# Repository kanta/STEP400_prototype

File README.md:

## STEP400_prototype

This repository has been retained for data storage, but is no longer being updated.

Please visit https://github.com/ponoor/STEP400.

---

STEP400 is a 4-axis stepper motor driver designed for art or design projects. STEP400 combines the following elements into one single board:

- [Arduino Zero](https://www.arduino.cc/en/Guide/ArduinoZero)
- Ethernet shield
- Four stepper motor drivers
- Sensor inputs for homing and limiting

The current firmware is focused on working with [Open Sound Control](http://opensoundcontrol.org/) (OSC) via Ethernet, which is a common protocol for creative coding environments, like openFrameworks, Processing, Max, Unity, or Touch Designer.

Stepper driver chips are STMicroelectronics's [powerSTEP01](https://www.st.com/en/motor-drivers/powerstep01.html) which provide most of functionalities as a stepper driver.

## Repository Contents

This repo is temporal place for working. All information will be moved to a new repo when the clean up is done.

### Firmware
[/rev4/STEP400_proto_r4_firmware/STEP400_proto_r4_firmware/](https://github.com/kanta/STEP400_prototype/tree/master/rev4/STEP400_proto_r4_firmware/STEP400_proto_r4_firmware)

Source files for the firmware. Some Visual Studio files are included but you can open .ino file with Arduino IDE.

### Hardware
[/rev4/hardware/](https://github.com/kanta/STEP400_prototype/tree/master/rev4/hardware)

PCB design files for Eagle.

## Firmware dependency
- **[OSC Library](https://github.com/CNMAT/OSC)** from CNMAT
- **[Ponoor PowerSTEP01 Library](https://github.com/ponoor/Ponoor_PowerSTEP01_Library)**
- **[ArduinoJSON Library](https://arduinojson.org/)**
- **[Adafruit SleepyDog Arduino Library](https://github.com/adafruit/Adafruit_SleepyDog)**

## Examples
### Max
https://github.com/kanta/STEP400_prototype/blob/master/rev4/STEP400_proto_r4.maxpat

### openFrameworks
https://github.com/ponoor/step-series-example-openFrameworks

### Unity
https://github.com/ponoor/step-series-example-Unity

### Touch Designer
https://github.com/ponoor/step-series-example-TouchDesigner

## Documentation
Now working on [Wiki](https://github.com/kanta/STEP400_prototype/wiki).

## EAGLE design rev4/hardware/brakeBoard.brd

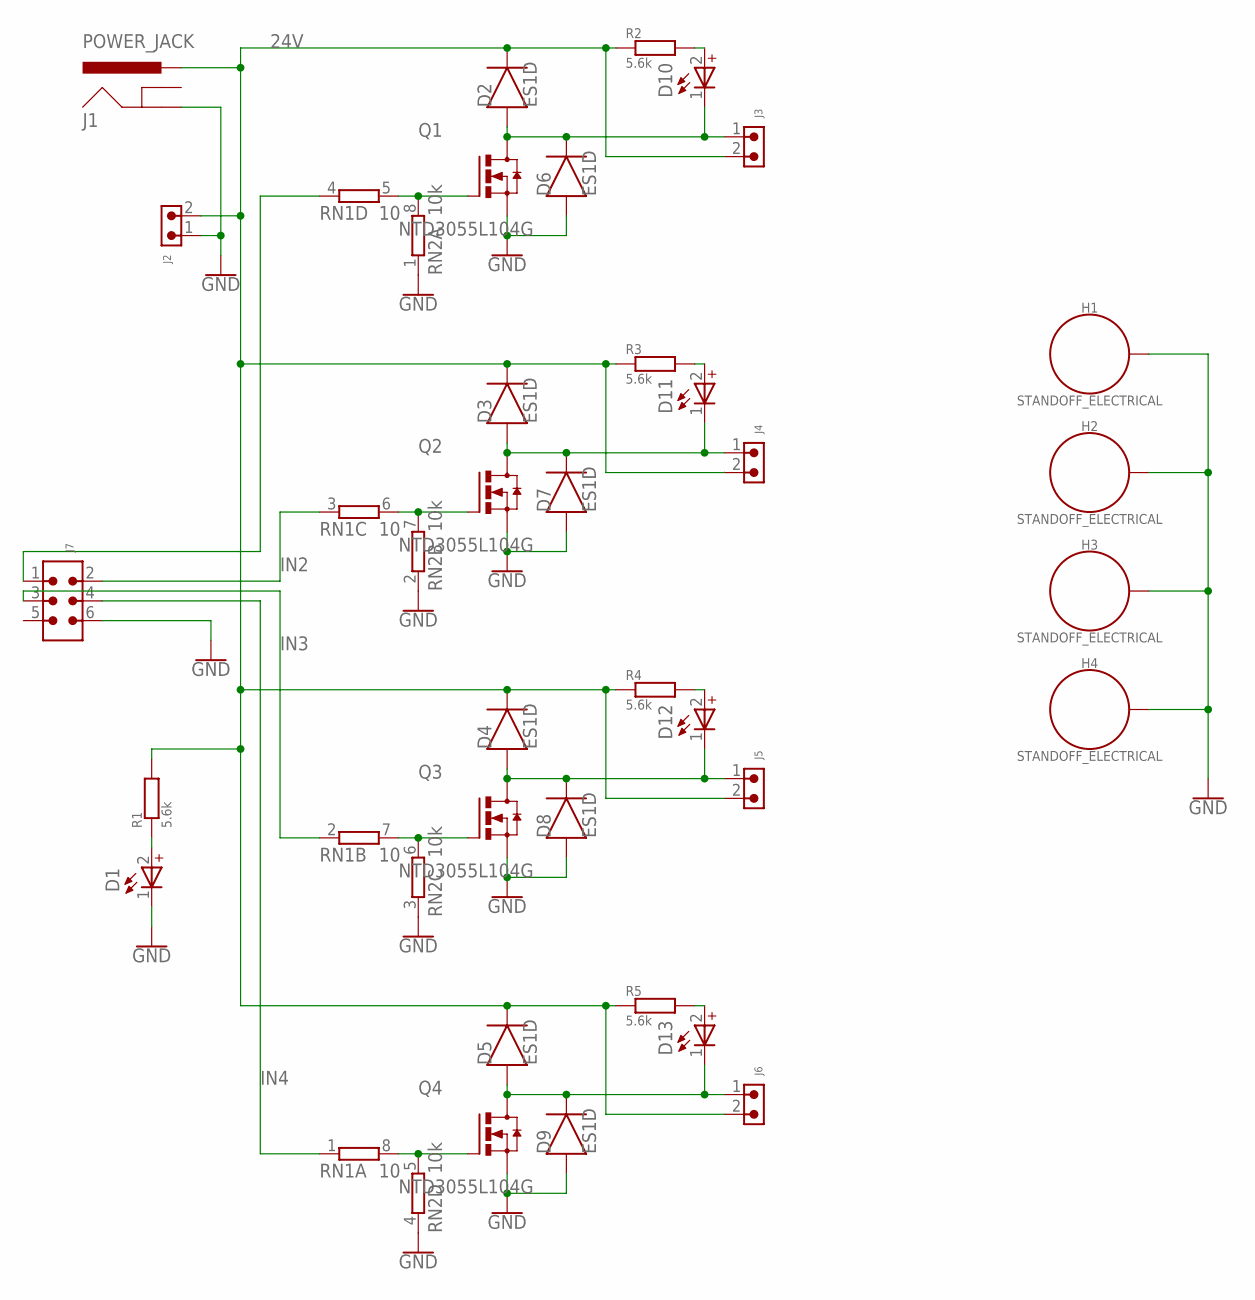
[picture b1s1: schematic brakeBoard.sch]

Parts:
D1, D10, D11, D12, D13: WL-SMCD_0603_150060GS55040; WL-SMCD_0603
D2, D3, D4, D5, D6, D7, D8, D9: ES1D; DIOM5226X290N
H1, H2, H3, H4: STANDOFF_ELECTRICAL; STANDOFF-ELECTRICAL
J1: POWER_JACK; POWER_JACK_PTH
J2: 691322310002
J3, J4, J5, J6: 691321300002
J7: 6120XX21621_61200621621; 61200621621
Q1, Q2, Q3, Q4: NTD3055L104G; DPAK3
R1, R2, R3, R4, R5: 5.6k; RESC2012X65
RN1: 10; CAY16_LONG_W
RN2: 10k; CAY16_LONG_W

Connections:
24V: D2.1 (C), D3.1 (C), D4.1 (C), D5.1 (C), J1.PWR, J2.2, J3.2, J4.2, J5.2, J6.2, R1.2, R2.1, R3.1, R4.1, R5.1
GND: D1.1 (_), D6.2 (A), D7.2 (A), D8.2 (A), D9.2 (A), H1.P1, H2.P1, H3.P1, H4.P1, J1.GND, J2.1, J7.6, Q1.2 (S), Q2.2 (S), Q3.2 (S), Q4.2 (S), RN2.1, RN2.2 (1), RN2.3 (1), RN2.4 (1)
IN1: J7.1, RN1.4 (1)
IN2: J7.2, RN1.3 (1)
IN3: J7.3, RN1.2 (1)
IN4: J7.4, RN1.1
unnamed: D2.2 (A), D6.1 (C), D10.1 (_), J3.1, Q1.3 (D)
unnamed: D10.2 (+), R2.2
unnamed: Q1.1 (G), RN1.5 (2), RN2.8 (2)
unnamed: D3.2 (A), D7.1 (C), D11.1 (_), J4.1, Q2.3 (D)
unnamed: D11.2 (+), R3.2
unnamed: D4.2 (A), D8.1 (C), D12.1 (_), J5.1, Q3.3 (D)
unnamed: D12.2 (+), R4.2
unnamed: D5.2 (A), D9.1 (C), D13.1 (_), J6.1, Q4.3 (D)
unnamed: D13.2 (+), R5.2
unnamed: Q4.1 (G), RN1.8 (2), RN2.5 (2)
unnamed: Q3.1 (G), RN1.7 (2), RN2.6 (2)
unnamed: Q2.1 (G), RN1.6 (2), RN2.7 (2)
unnamed: D1.2 (+), R1.1

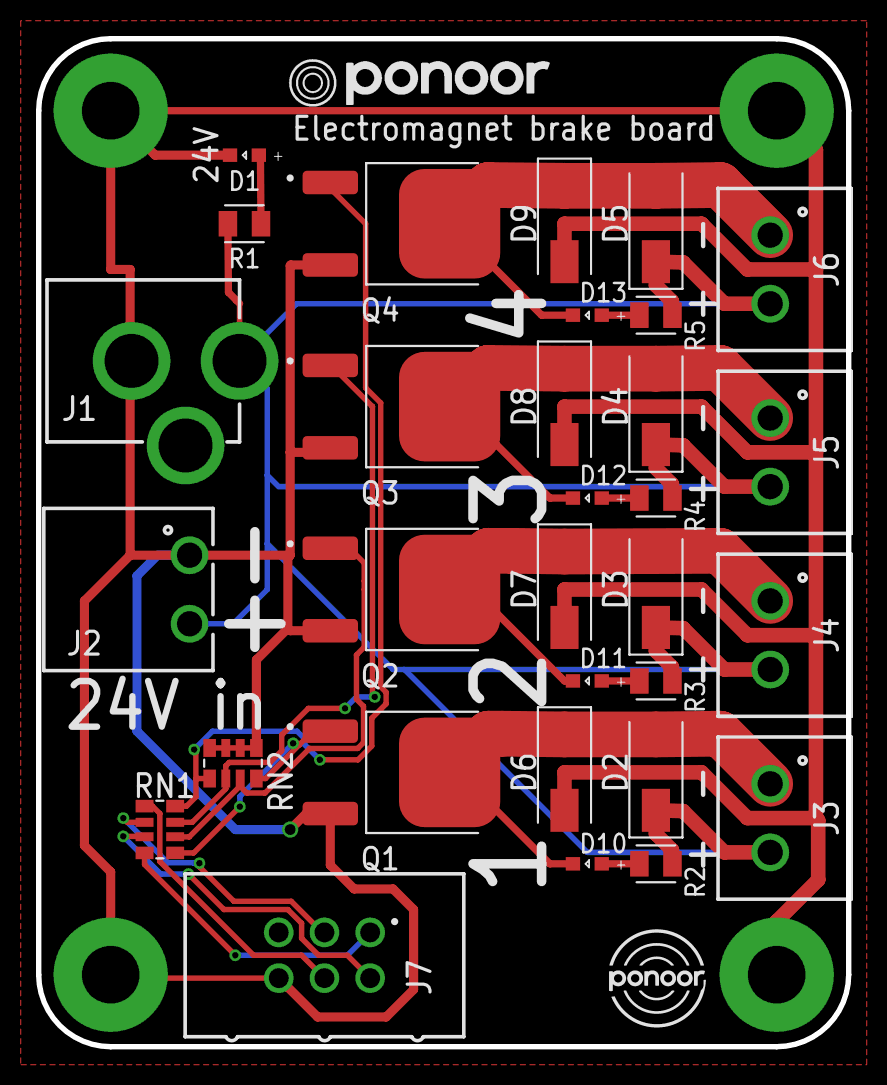
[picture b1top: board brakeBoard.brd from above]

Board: 2 copper layers, 45.0 x 56.0 mm, 38 parts (1 on the bottom side), 19 nets.

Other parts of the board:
U$1: PONOOR_LOGO_6MM
U$2, U$3: PONOOR_TEXT_15MM

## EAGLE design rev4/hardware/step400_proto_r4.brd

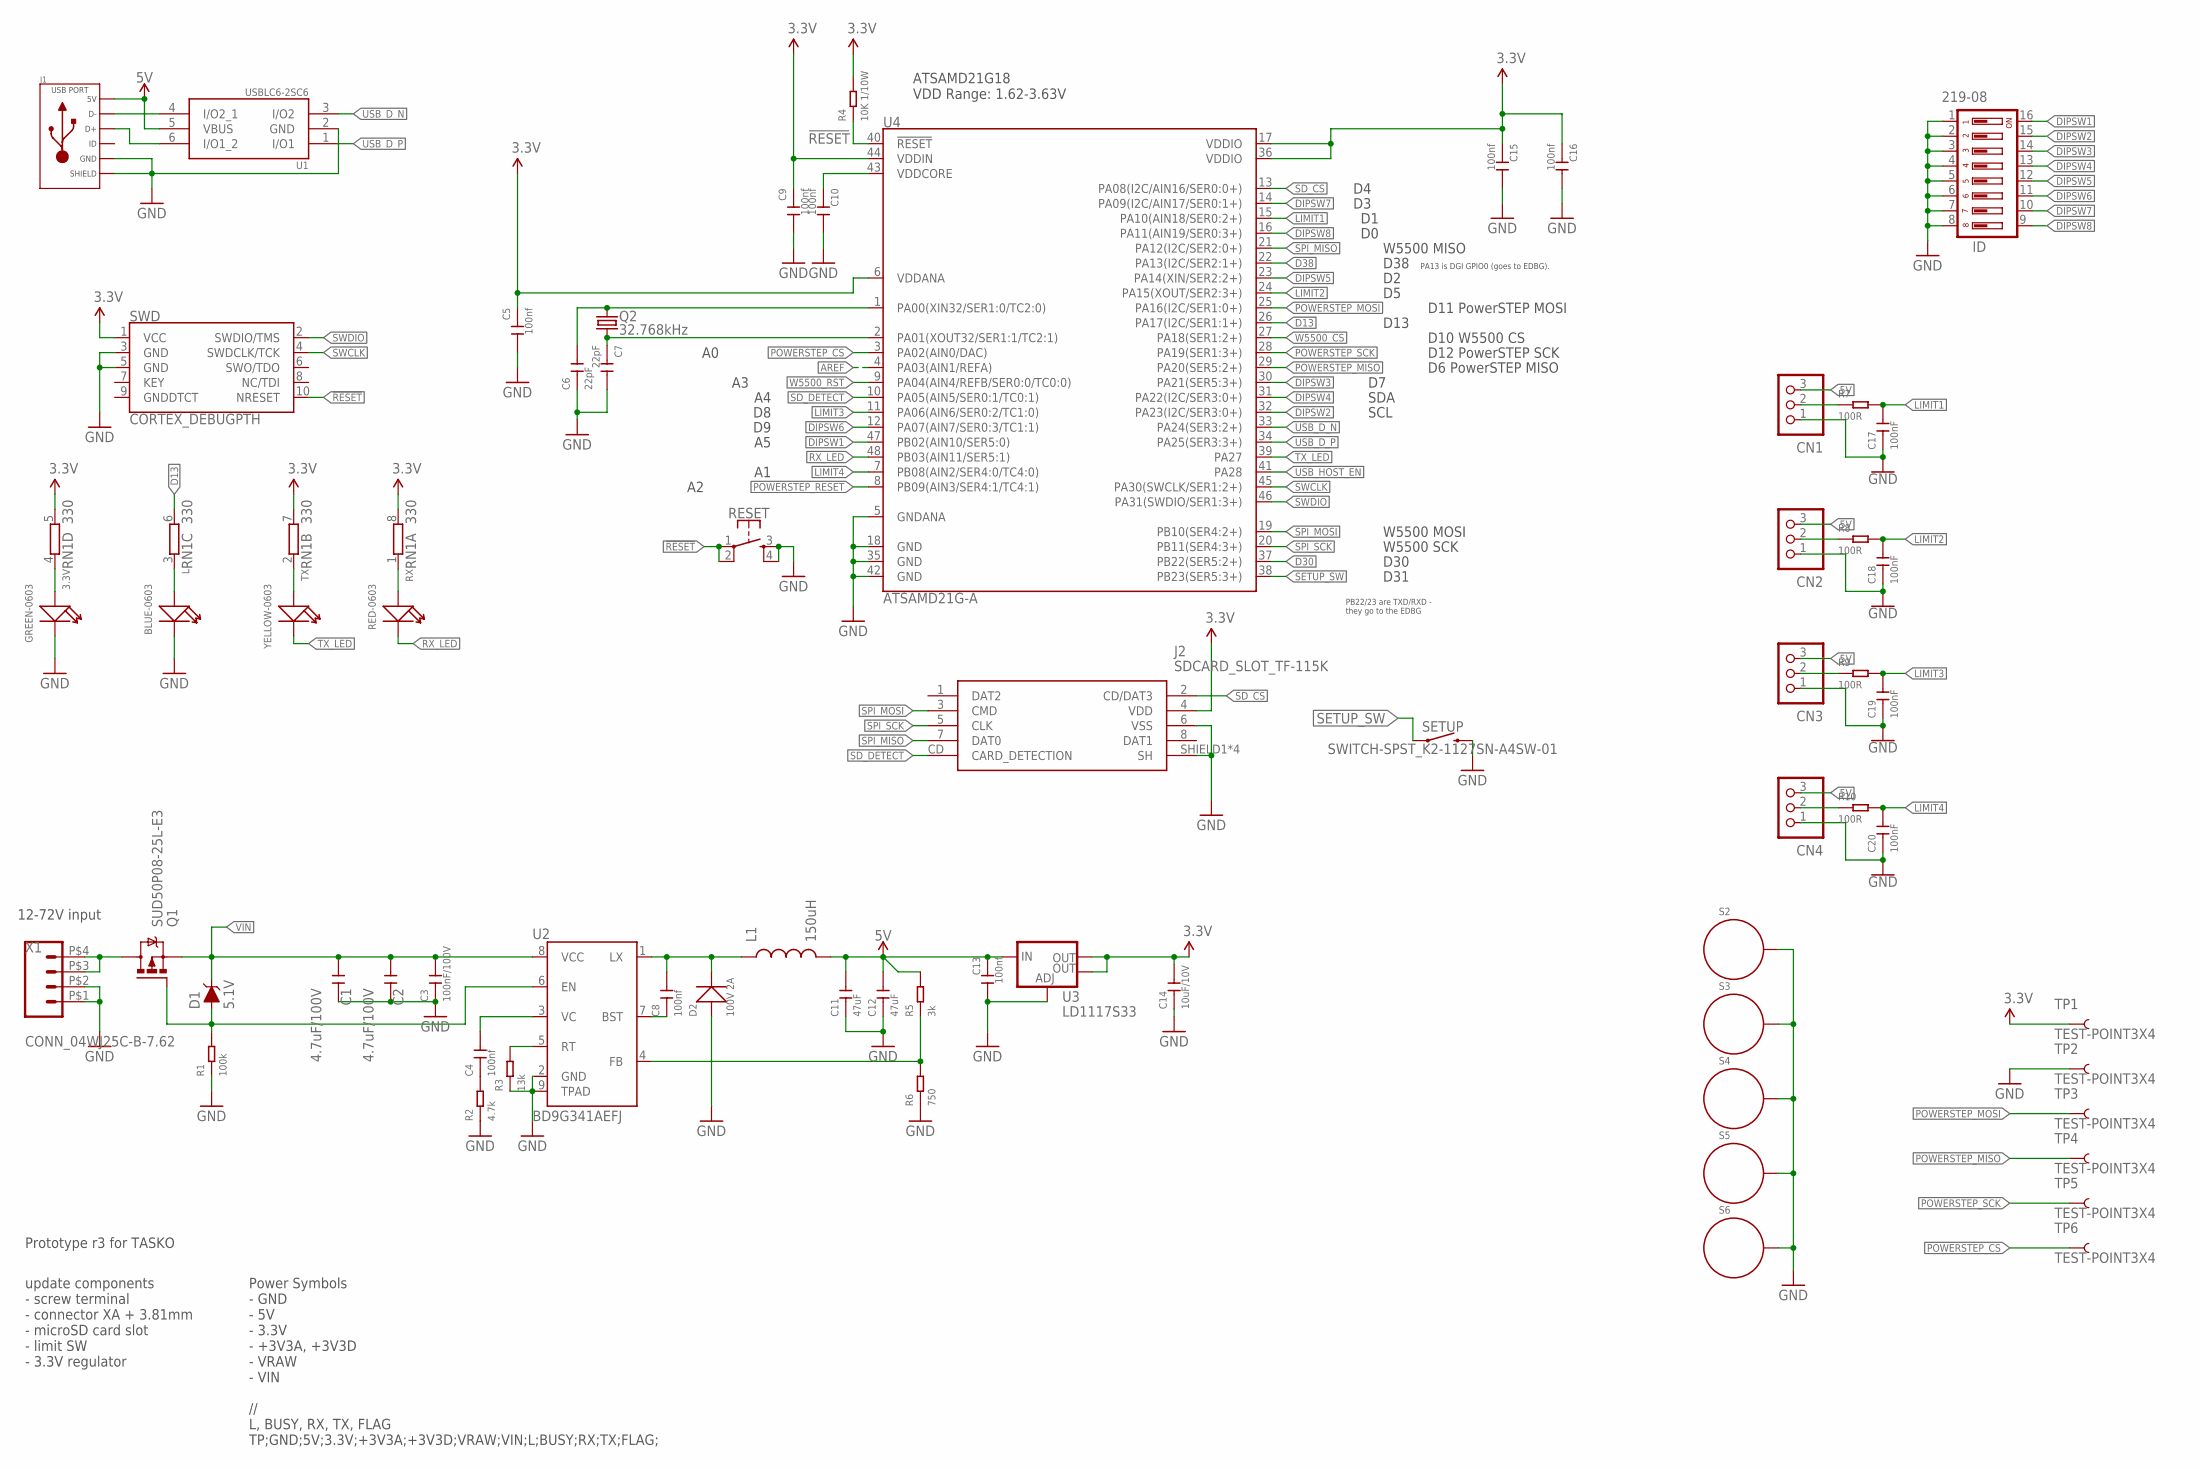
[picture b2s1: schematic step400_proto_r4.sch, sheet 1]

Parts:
3.3V: GREEN-0603; LED-0603
C1, C2: 4.7uF/100V; C1210
C3: 100nF/100V; C0805
C4, C8: 100nf; C0603
C5, C9, C10, C13, C15, C16: 100nf; C0402
C6, C7: 22pF; C0402
C11, C12: 47uF; C1206
C14: 10uF/10V; C0805
C17, C18, C19, C20: 100nF; C0402
CN1, CN2, CN3, CN4: B3B-XASK-1
D1: 5.1V; SOD-323
D2: 100V 2A; DO-214AC
ID: 219-08; CTS-219-08
J1: USB_MICRO_10118193-0001LF; MICROUSB-FCI-PBAN
J2: SDCARD_SLOT_TF-115K; TF-115K
L: BLUE-0603; LED-0603
L1: 150uH; L5045_L
Q1: SUD50P08-25L-E3; D-PAK_TO252AA
Q2: 32.768kHz; FC-135
R1: 100k; R0603
R2: 4.7k; R0603
R3: 13k; R0603
R4: 10K 1/10W; R0603
R5: 3k; R0603
R6: 750; R0603
R7, R8, R9, R10: 100R; R0603
RESET: MOMENTARY-SWITCH-SPST-2-SMD-5.2MM; TACTILE_SWITCH_SMD_5.2MM
RN1: 330; CAY16_LONG_W
RX: RED-0603; LED-0603
S2, S3, S4, S5, S6: STANDOFF_ELECTRICAL; STANDOFF-ELECTRICAL
SETUP: SWITCH-SPST_K2-1127SN-A4SW-01; K2-1127SN-A4SW-01
SWD: CORTEX_DEBUGPTH; 2X5-PTH-1.27MM
TP1, TP2, TP3, TP4, TP5, TP6: TEST-POINT3X4; PAD.03X.04
TX: YELLOW-0603; LED-0603
U1: USBLC6-2SC6; SOT23-6L
U2: BD9G341AEFJ; SOIC127P600X100-9N
U3: LD1117S33; SOT223
U4: ATSAMD21G-A; TQFP-48
X1: CONN_04WJ25C-B-7.62; WJ25C-B-7.62-4P

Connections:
3.3V: C5.1, C9.1, C14.2, C15.1, C16.1, J2.4 (VDD), R4.2, RN1.5 (2), RN1.7 (2), RN1.8 (2), SWD.1 (VCC), TP1.P$1, U3.2 (OUT), U3.4 (OUT), U4.6 (VDDANA), U4.17 (VDDIO), U4.36 (VDDIO), U4.44 (VDDIN); also elsewhere on the board
5V: C11.2, C12.2, C13.1, CN1.3, CN2.3, CN3.3, CN4.3, J1.1 (5V), L1.P$2 (2), R5.2, U1.5 (VBUS), U3.3 (IN); also elsewhere on the board
!RESET: R4.1, RESET.1, RESET.2, SWD.10 (NRESET), U4.40 (!RESET!)
AREF: U4.4 (PA03(AIN1/REFA))
D13: RN1.6 (2), U4.26 (PA17(I2C/SER1:1+))
D30: U4.37 (PB22(SER5:2+))
D38: U4.22 (PA13(I2C/SER2:1+))
D+: J1.3 (D+), U1.6 (I/O1_2)
DIPSW1: ID.16, U4.47 (PB02(AIN10/SER5:0))
DIPSW2: ID.15, U4.32 (PA23(I2C/SER3:0+))
DIPSW3: ID.14, U4.30 (PA21(SER5:3+))
DIPSW4: ID.13, U4.31 (PA22(I2C/SER3:0+))
DIPSW5: ID.12, U4.23 (PA14(XIN/SER2:2+))
DIPSW6: ID.11, U4.12 (PA07(AIN7/SER0:3/TC1:1))
DIPSW7: ID.10, U4.14 (PA09(I2C/AIN17/SER0:1+))
DIPSW8: ID.9, U4.16 (PA11(AIN19/SER0:3+))
GND: 3.3V.-, C1.2, C2.2, C3.1, C5.2, C6.1, C7.2, C9.2, C10.2, C11.1, C12.1, C13.2, C14.1, C15.2, C16.2, C17.1, C18.1, C19.1, C20.1, CN1.1, CN2.1, CN3.1, CN4.1, D2.1 (+), ID.1, ID.2, ID.3, ID.4, ID.5, ID.6, ID.7, ID.8, J1.5 (GND), J1.S1 (SLD), J1.S2 (SLD), J1.S3 (SLD), J1.S4 (SLD), J1.S5 (SLD), J1.S6 (SLD), J1.S7 (SLD), J1.S8 (SLD), J2.6 (VSS), J2.SHIELD1 (SH), J2.SHIELD2 (SH), J2.SHIELD3 (SH), J2.SHIELD4 (SH), L.-, R1.1, R2.1, R3.1, R6.1, RESET.3, RESET.4, S2.P1, S3.P1, S4.P1, S5.P1, S6.P1, SETUP.P$3 (2), SETUP.P$4 (2), SWD.3 (GND), SWD.5 (GND), TP2.P$1, U1.2 (GND), U2.2 (GND), U2.9 (TPAD), U3.1 (ADJ), U4.5 (GNDANA), U4.18 (GND), U4.35 (GND), U4.42 (GND), X1.P$1 (1), X1.P$2 (2); also elsewhere on the board
LIMIT1: C17.2, R7.2, U4.15 (PA10(AIN18/SER0:2+))
LIMIT2: C18.2, R8.2, U4.24 (PA15(XOUT/SER2:3+))
LIMIT3: C19.2, R9.2, U4.11 (PA06(AIN6/SER0:2/TC1:0))
LIMIT4: C20.2, R10.2, U4.7 (PB08(AIN2/SER4:0/TC4:0))
unnamed: C6.2, Q2.P$2 (2), U4.1 (PA00(XIN32/SER1:0/TC2:0))
unnamed: C4.1, R2.2
unnamed: C7.1, Q2.P$1 (1), U4.2 (PA01(XOUT32/SER1:1/TC2:1))
unnamed: RN1.1, RX.+
unnamed: RN1.2 (1), TX.+
unnamed: R5.1, R6.2, U2.4 (FB)
unnamed: D1.A, Q1.1 (G), R1.2, U2.6 (EN)
unnamed: R3.2, U2.5 (RT)
unnamed: L.+, RN1.3 (1)
unnamed: 3.3V.+, RN1.4 (1)
unnamed: C4.2, U2.3 (VC)
unnamed: CN1.2, R7.1
unnamed: C8.1, U2.7 (BST)
unnamed: CN2.2, R8.1
unnamed: C8.2, D2.2 (-), L1.P$1 (1), U2.1 (LX)
unnamed: CN3.2, R9.1
unnamed: CN4.2, R10.1
unnamed: J1.2 (D-), U1.4 (I/O2_1)
POWERSTEP_CS: TP6.P$1, U4.3 (PA02(AIN0/DAC)); also elsewhere on the board
POWERSTEP_MISO: TP4.P$1, U4.29 (PA20(SER5:2+)); also elsewhere on the board
POWERSTEP_MOSI: TP3.P$1, U4.25 (PA16(I2C/SER1:0+)); also elsewhere on the board
POWERSTEP_RESET: U4.8 (PB09(AIN3/SER4:1/TC4:1)); also elsewhere on the board
POWERSTEP_SCK: TP5.P$1, U4.28 (PA19(SER1:3+)); also elsewhere on the board
RX_LED: RX.-, U4.48 (PB03(AIN11/SER5:1))
SD_CS: J2.2 (CD/DAT3), U4.13 (PA08(I2C/AIN16/SER0:0+))
SD_DETECT: J2.CD (CARD_DETECTION), U4.10 (PA05(AIN5/SER0:1/TC0:1))
SETUP_SW: SETUP.P$1 (1), SETUP.P$2 (1), U4.38 (PB23(SER5:3+))
SPI_MISO: J2.7 (DAT0), U4.21 (PA12(I2C/SER2:0+)); also elsewhere on the board
SPI_MOSI: J2.3 (CMD), U4.19 (PB10(SER4:2+)); also elsewhere on the board
SPI_SCK: J2.5 (CLK), U4.20 (PB11(SER4:3+)); also elsewhere on the board
SWCLK: SWD.4 (SWDCLK/TCK), U4.45 (PA30(SWCLK/SER1:2+))
SWDIO: SWD.2 (SWDIO/TMS), U4.46 (PA31(SWDIO/SER1:3+))
TX_LED: TX.-, U4.39 (PA27)
USB_D_N: U1.3 (I/O2), U4.33 (PA24(SER3:2+))
USB_D_P: U1.1 (I/O1), U4.34 (PA25(SER3:3+))
USB_HOST_EN: U4.41 (PA28)
VDDCORE: C10.1, U4.43 (VDDCORE)
VIN: C1.1, C2.1, C3.2, D1.C, Q1.3 (S), U2.8 (VCC); also elsewhere on the board
VRAW: Q1.4 (D), X1.P$3 (3), X1.P$4 (4)
W5500_CS: U4.27 (PA18(SER1:2+)); also elsewhere on the board
W5500_RST: U4.9 (PA04(AIN4/REFB/SER0:0/TC0:0)); also elsewhere on the board

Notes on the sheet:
PB22/23 are TXD/RXD - they go to the EDBG
PA13 is DGI GPIO0 (goes to EDBG).
ATSAMD21G18 VDD Range: 1.62-3.63V
D30
D12 PowerSTEP SCK
D10 W5500 CS
D11 PowerSTEP MOSI
D13
D6 PowerSTEP MISO
D38
12-72V input
W5500 MISO
W5500 MOSI
W5500 SCK
SDA
SCL
D31
Prototype r3 for TASKO
update components - screw terminal - connector XA + 3.81mm - microSD card slot - limit SW - 3.3V regulator
Power Symbols - GND - 5V - 3.3V - +3V3A, +3V3D - VRAW - VIN // L, BUSY, RX, TX, FLAG TP;GND;5V;3.3V;+3V3A;+3V3D;VRAW;VIN;L;BUSY;RX;TX;FLAG;

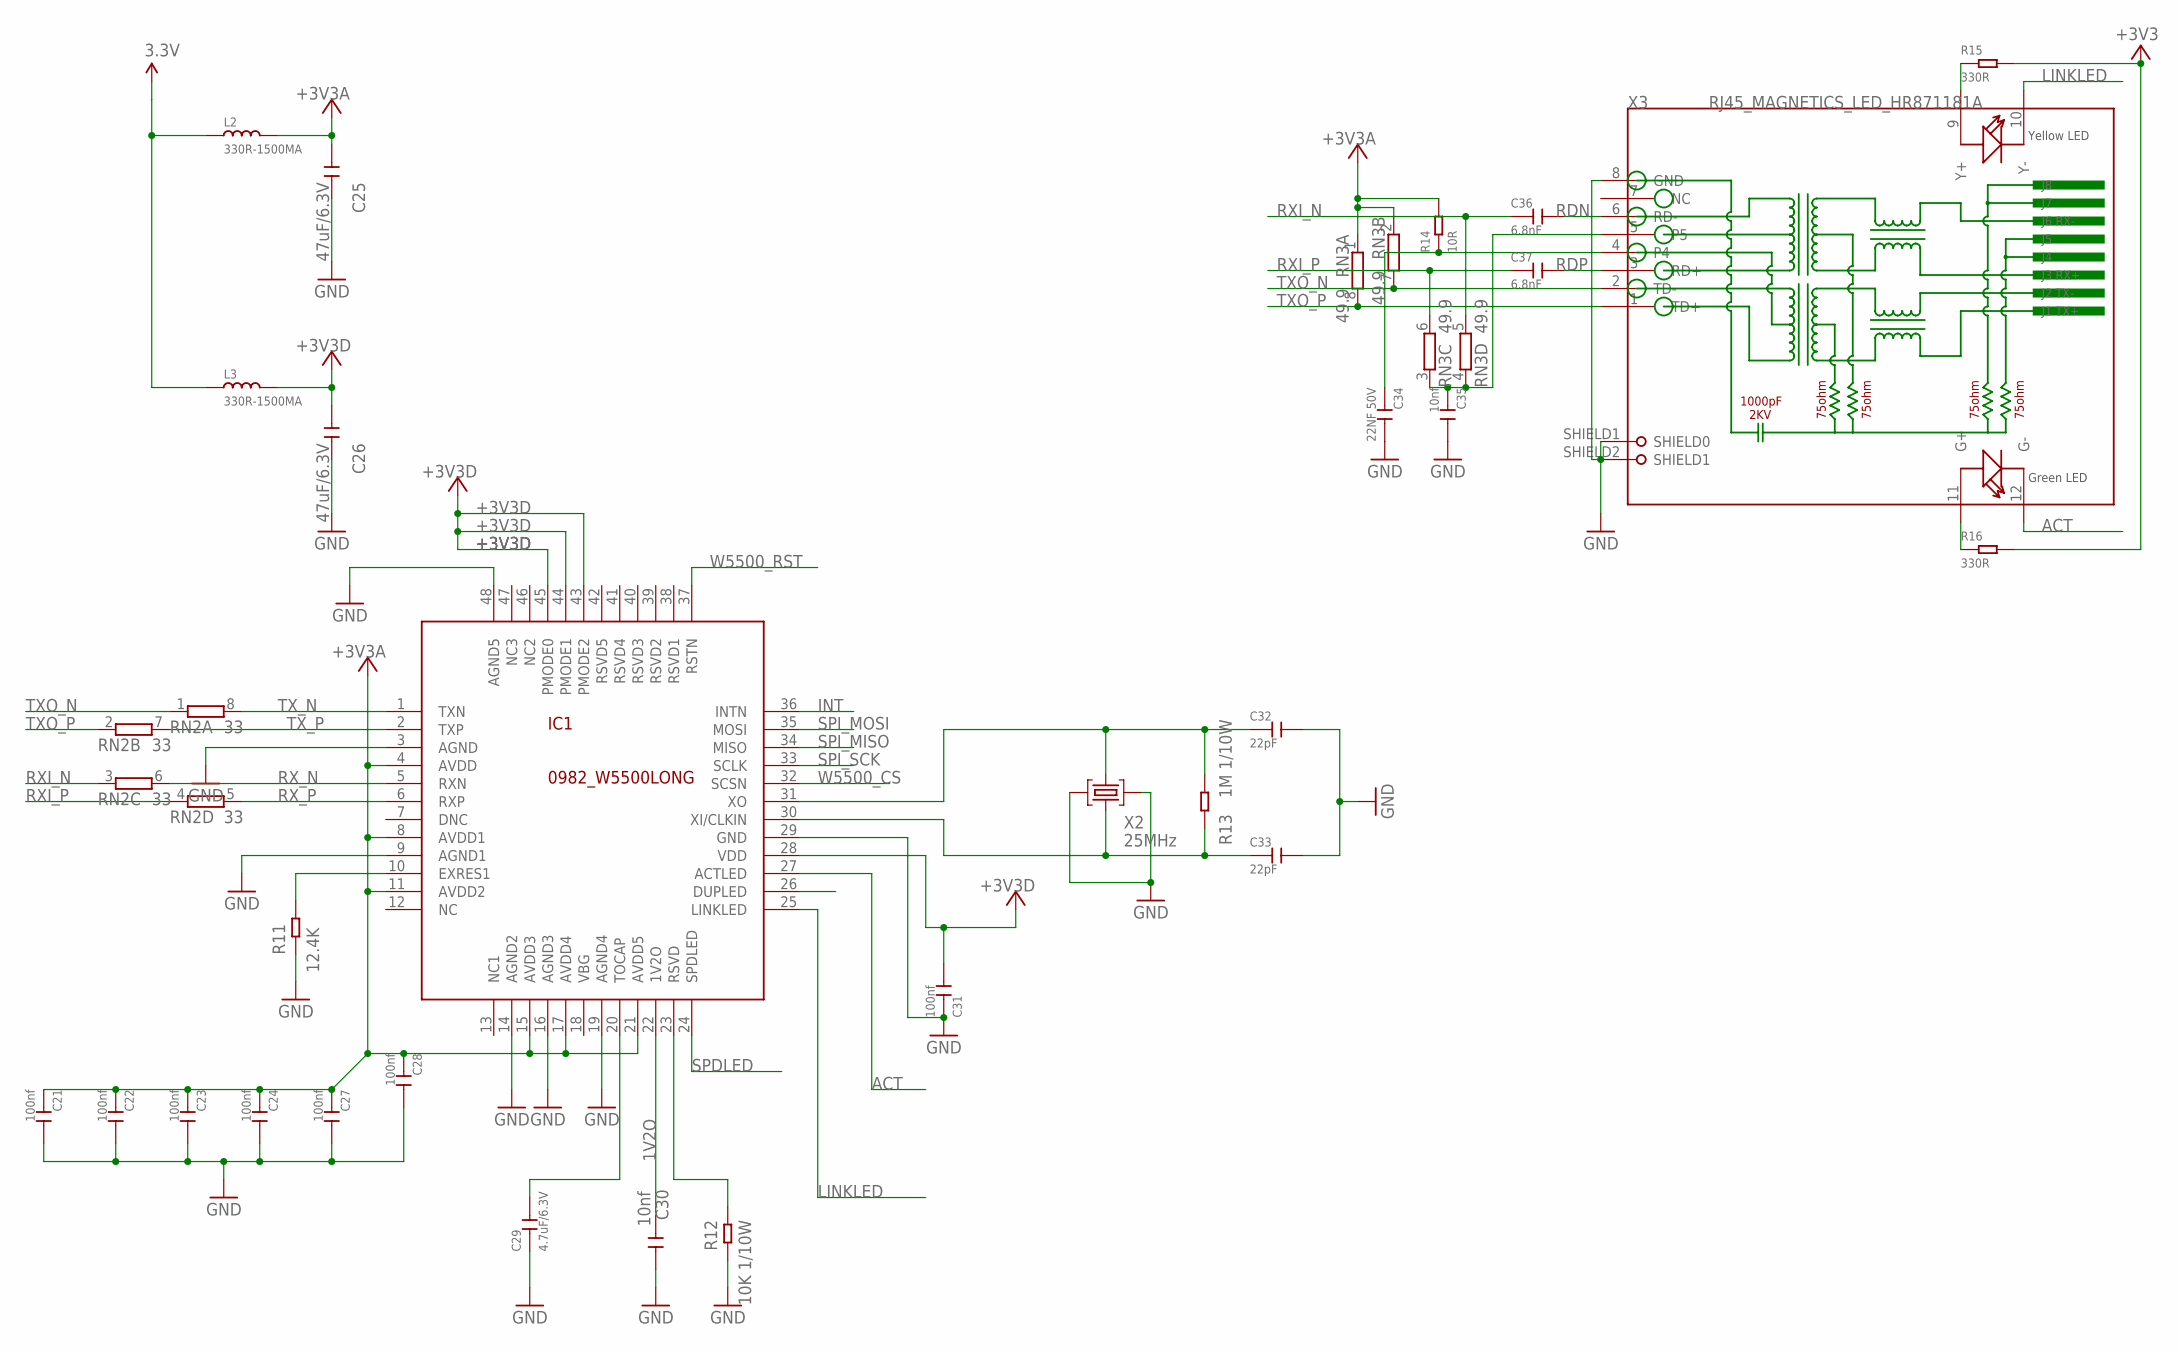
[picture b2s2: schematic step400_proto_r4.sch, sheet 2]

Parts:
C21, C22, C23, C24, C27, C28, C31: 100nf; C0402
C25, C26: 47uF/6.3V; C1206
C29: 4.7uF/6.3V; C0603
C30, C35: 10nf; C0402
C32, C33: 22pF; C0402
C34: 22NF 50V; C0402
C36, C37: 6.8nF; C0402
IC1: 0982_W5500LONG; TQFP48-LONG
L2, L3: 330R-1500MA; L0805
R11: 12.4K; R0603
R12: 10K 1/10W; R0603
R13: 1M 1/10W; R0603
R14: 10R; R0603
R15, R16: 330R; R0603
RN2: 33; CAY16_LONG_W
RN3: 49.9; CAY16_LONG_W
X2: 25MHz; CRYSTAL-3.2-2.5
X3: RJ45_MAGNETICS_LED_HR871181A; HR871181A

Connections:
1V2O: C30.2, IC1.22 (1V2O)
3.3V: L2.1, L3.1, R15.2, R16.2; also elsewhere on the board
+3V3A: C21.1, C22.1, C23.1, C24.1, C25.1, C27.1, C28.1, IC1.4 (AVDD), IC1.8 (AVDD1), IC1.11 (AVDD2), IC1.15 (AVDD3), IC1.17 (AVDD4), IC1.21 (AVDD5), L2.2, R14.2, RN3.1, RN3.2 (1)
+3V3D: C26.1, C31.2, IC1.28 (VDD), IC1.43 (PMODE2), IC1.44 (PMODE1), IC1.45 (PMODE0), L3.2
ACT: IC1.27 (ACTLED), X3.12 (G-)
FDXLED: IC1.26 (DUPLED)
GND: C21.2, C22.2, C23.2, C24.2, C25.2, C26.2, C27.2, C28.2, C29.1, C30.1, C31.1, C32.2, C33.2, C34.2, C35.2, IC1.3 (AGND), IC1.9 (AGND1), IC1.14 (AGND2), IC1.16 (AGND3), IC1.19 (AGND4), IC1.29 (GND), IC1.48 (AGND5), R11.1, R12.1, X2.2 (GND), X2.4 (GND), X3.8 (GND), X3.SHIELD1 (SHIELD0), X3.SHIELD2 (SHIELD1); also elsewhere on the board
INT: IC1.36 (INTN)
LINKLED: IC1.25 (LINKLED), X3.10 (Y-)
unnamed: C32.1, IC1.31 (XO), R13.1, X2.3 (C2)
unnamed: C34.1, R14.1, X3.4
unnamed: C35.1, RN3.3 (1), RN3.4 (1), X3.5
unnamed: R15.1, X3.9 (Y+)
unnamed: R16.1, X3.11 (G+)
unnamed: IC1.23 (RSVD), R12.2
unnamed: C29.2, IC1.20 (TOCAP)
unnamed: IC1.10 (EXRES1), R11.2
NC: IC1.12 (NC)
OSC2E2: C33.1, IC1.30 (XI/CLKIN), R13.2, X2.1 (C1)
RDN: C36.2, X3.6 (RD-)
RDP: C37.2, X3.3 (RD+)
RSVD1: IC1.38 (RSVD1)
RSVD2: IC1.39 (RSVD2)
RSVD3: IC1.40 (RSVD3)
RXI_N: C36.1, RN2.3 (1), RN3.5 (2)
RXI_P: C37.1, RN2.4 (1), RN3.6 (2)
RX_N: IC1.5 (RXN), RN2.6 (2)
RX_P: IC1.6 (RXP), RN2.5 (2)
SPDLED: IC1.24 (SPDLED)
SPI_MISO: IC1.34 (MISO); also elsewhere on the board
SPI_MOSI: IC1.35 (MOSI); also elsewhere on the board
SPI_SCK: IC1.33 (SCLK); also elsewhere on the board
TXO_N: RN2.1, RN3.7 (2), X3.2 (TD-)
TXO_P: RN2.2 (1), RN3.8 (2), X3.1 (TD+)
TX_N: IC1.1 (TXN), RN2.8 (2)
TX_P: IC1.2 (TXP), RN2.7 (2)
W5500_CS: IC1.32 (SCSN); also elsewhere on the board
W5500_RST: IC1.37 (RSTN); also elsewhere on the board

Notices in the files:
parts and their libraries:
Wurth_LEDs_WL-SMCD: Copyright: Würth Elektronik
SparkFun-Hardware: Licensing: Creative Commons ShareAlike 4.0 International - https://creativecommons.org/licenses/by-sa/4.0
